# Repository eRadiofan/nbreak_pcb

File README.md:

# nbreak_pcb

This is an Econet transceiver PCB designed for [the n-break project](https://github.com/banksy-git/nbreak-econet), using Kicad. Currently, only the [eRadiofan fork](https://github.com/eRadiofan/nbreak-econet) is compatible and tested as working with this PCB.

The board is intended to be soldered to an ESP32-C6 module, the following are know to fit:

- Waveshare ESP32-C6 Development Board
- Diymore ESP32-C6-WROOM1 Module

Many others have a suitable pinout.

The board hosts 2 MAX485 chips running at 5V with level shifters for interfacing with the ESP32-C6.

Connection is via 5-pin DIN and/or 5-pin header.

Internal/external clock selection is via the UI. There is a link for enabling on-board terminators and a jumper option for enabling selection via the UI in the future.

There is a blue LED for indication of a clock signal and a bi-colour LED for indication of transmission and reception. They are designed as 3mm through-hole types intended for poking through holes in a case (TBD).

The PCB is only 31mm wide and 44mm long.

Version 1 assembled (wired direct to header) and soldered to ESP32-C6 board:

Version 2 contains a correction to the footprint of IC U3 and has a connection to D10 instead of D8.

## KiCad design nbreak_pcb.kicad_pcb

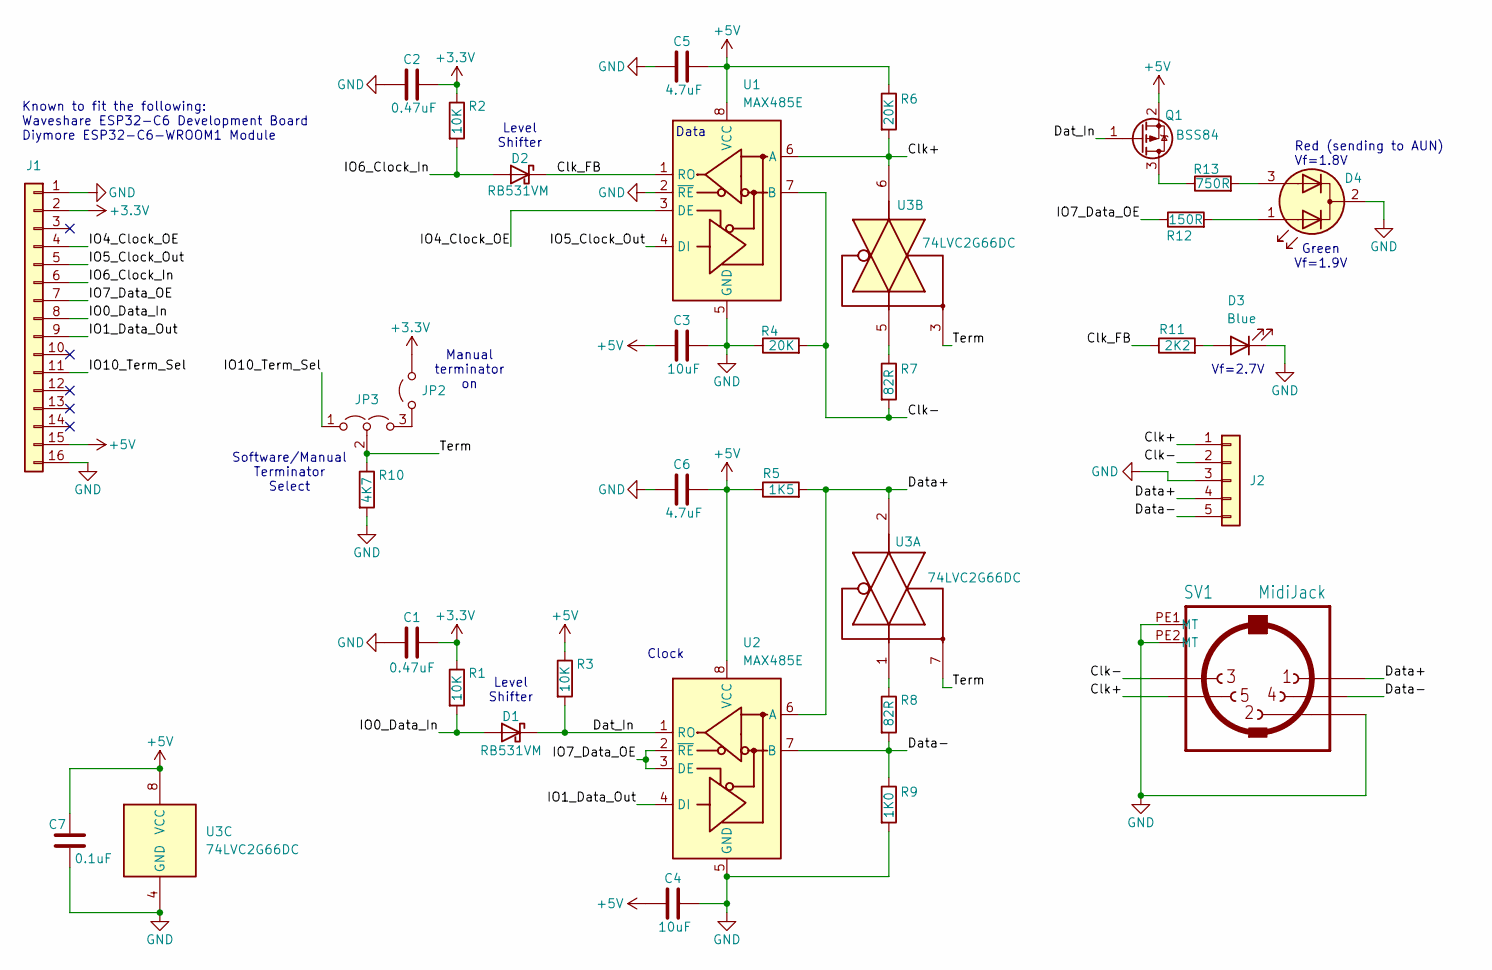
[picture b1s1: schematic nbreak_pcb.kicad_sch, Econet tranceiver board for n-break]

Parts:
C1, C2: 0.47uF; C_0805_2012Metric_Pad1.18x1.45mm_HandSolder
C3, C4: 10uF; C_0805_2012Metric_Pad1.18x1.45mm_HandSolder
C5, C6: 4.7uF; C_0805_2012Metric_Pad1.18x1.45mm_HandSolder
C7: 0.1uF; C_0603_1608Metric_Pad1.08x0.95mm_HandSolder
D1, D2: RB531VM; D_SOD-323F
D3: Blue; LED_D3.0mm
D4: LED_Dual_AAK; LED_D3.0mm-3
J1: Conn_01x16; PinHeader_1x16_P2.54mm_Vertical
J2: Conn_01x05; PinHeader_1x05_P2.54mm_Vertical
JP2: Jumper_2_Open; PinHeader_1x02_P2.54mm_Vertical
JP3: Jumper_3_Open; SolderJumper-3_P1.3mm_Open_RoundedPad1.0x1.5mm
Q1: BSS84; SOT-23
R1, R2, R3: 10K; R_0805_2012Metric_Pad1.20x1.40mm_HandSolder
R4, R6: 20K; R_0805_2012Metric_Pad1.20x1.40mm_HandSolder
R5: 1K5; R_0805_2012Metric_Pad1.20x1.40mm_HandSolder
R7, R8: 82R; R_0805_2012Metric_Pad1.20x1.40mm_HandSolder
R9: 1K0; R_0805_2012Metric_Pad1.20x1.40mm_HandSolder
R10: 4K7; R_0805_2012Metric_Pad1.20x1.40mm_HandSolder
R11: 2K2; R_0805_2012Metric_Pad1.20x1.40mm_HandSolder
R12: 150R; R_0805_2012Metric_Pad1.20x1.40mm_HandSolder
R13: 750R; R_0805_2012Metric_Pad1.20x1.40mm_HandSolder
SV1: MidiJack; MidiConnector
U1, U2: MAX485E; SOIC-8_3.9x4.9mm_P1.27mm
U3: 74LVC2G66DC; VSSOP-8_2.3x2mm_P0.5mm

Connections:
+3.3V: C1.2, C2.2, J1.2, JP2.2 (B), R1.1, R2.1
+5V: C3.1, C4.1, C5.2, C6.2, C7.2, J1.15, Q1.2 (S), R3.1, R5.1, R6.1, U1.8 (VCC), U2.8 (VCC), U3.8 (VCC)
/Clk+: J2.1, R6.2, SV1.5, U1.6 (A), U3.6
/Clk-: J2.2, R4.2, R7.2, SV1.3, U1.7 (B)
/Clk_FB: D2.1 (K), R11.1, U1.1 (RO)
/Dat_In: D1.1 (K), Q1.1 (G), R3.2, U2.1 (RO)
/Data+: J2.4, R5.2, SV1.1, U2.6 (A), U3.2
/Data-: J2.5, R8.2, R9.1, SV1.4, U2.7 (B)
/IO0_Data_In: D1.2 (A), J1.8, R1.2
/IO1_Data_Out: J1.9, U2.4 (DI)
/IO4_Clock_OE: J1.4, U1.3 (DE)
/IO5_Clock_Out: J1.5, U1.4 (DI)
/IO6_Clock_In: D2.2 (A), J1.6, R2.2
/IO7_Data_OE: J1.7, R12.1, U2.2 (~RE), U2.3 (DE)
/IO10_Term_Sel: J1.11, JP3.1 (A)
/Term: JP3.2 (C), R10.1, U3.3, U3.7
GND: C1.1, C2.1, C3.2, C4.2, C5.1, C6.1, C7.1, D3.1 (K), D4.2 (K), J1.1, J1.16, J2.3, R4.1, R9.2, R10.2, SV1.2, SV1.PE1 (MT), SV1.PE2 (MT), U1.2 (~RE), U1.5 (GND), U2.5 (GND), U3.4 (GND)
unnamed: D3.2 (A), R11.2
unnamed: D4.1 (A1), R12.2
unnamed: D4.3 (A2), R13.2
unnamed: JP2.1 (A), JP3.3 (B)
unnamed: Q1.3 (D), R13.1
unnamed: R7.1, U3.5
unnamed: R8.1, U3.1

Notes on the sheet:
Red (sending to AUN) Vf=1.8V
Level Shifter
Manual terminator on
Software/Manual Terminator Select
Known to fit the following: Waveshare ESP32-C6 Development Board Diymore ESP32-C6-WROOM1 Module
Clock
Data
Green Vf=1.9V
Vf=2.7V

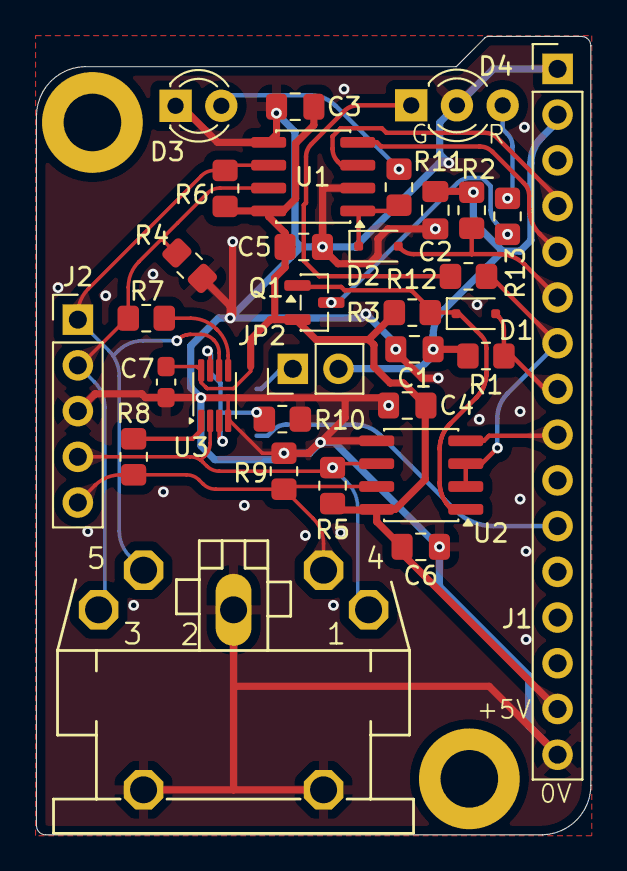
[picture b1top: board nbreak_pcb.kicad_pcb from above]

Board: 2 copper layers, 30.8 x 44.4 mm, 33 parts (1 on the bottom side), 24 nets.

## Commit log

2025-12-10 Initial version
2025-12-10 Added screenshot
2025-12-10 Fixed data polarity at DIN socket
2025-12-10 Update schematic image following fix
2025-12-11 Simplified clock and terminator selection
2025-12-12 Added activity indicator LEDs
2025-12-24 Updates for version 2, following construction of first prototype
2026-01-03 Updates to README, images and added a photo of aseembled PCB
